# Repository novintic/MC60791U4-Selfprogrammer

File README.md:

This is a take at the MC68701/U4 self- programmer board published in application note AN906A/D by Motorola in 1987.

It allows the 'self-programming' of the MC68701(U4) microcontroller (basically an 6801 with built in Eprom).

Probably the only conceivable use for this thing nowadays is to program a 68701U4 to be used as a replacement for the custom 'PS4' chip on a Bubble Bobble arcade PCB. But if you read this you'll most likely already know that.

MC68701U4s are still more or less readily available on Ebay (either NOS or used).

Some additions and modifications to the original design have been made:
 - redesigned the power supply for the +21V programming voltage using an MC34063 based boost converter circuit
 - uses 27C512 ROMS as these are easily available and dirt cheap
 - Added a Vpp- Voltage LED: will light dim when 5V present and bright wenn 21V Vpp is switched on.

Usage: 
 - Eprom U3 must be programmed with the minprgu4.bin which contains the selfprogramming- code
 - Eprom U4 contains the image to be programmed to the MCU's Eprom (most likely 'a78-01.17' found in the 'bin'- folder).
 - Turn off Power (SW1), put SW2 in 'RESET' position
 - Insert the MC68701U4
 - Switch power on.'PWR' LED should light. 'Vpp' LED will be off (indicating /RST is low)
 - Switch SW2 to 'PRGRM'. 'Vpp' will light dim indicating 5V present at /RST which will take the MCU out of reset and rum minprgu4. At the same time LED 'BLANK' should light indicating blank check. If this check fails, both 'BLANK' and 'FAIL' LEDs will light.
 - If blank- check passes, minprgu4 will switch on Vpp. 'Vpp'- LED will light brightly. Programming of the MCU starts and will take approximately 4 minutes.
 - If programming was successful - which means that the data has been verified correctly - LED 'PASS' will light. If not, LED 'FAIL' will light.

-----------------------------------------------------------------------------------------------
IMPORTANT!

MINPRGU4 must be located from $1850-$1FFF on EPROM U3 (NOT starting from $1800 as the instructions in 'Self-Programming the MC68701/U4 document could be understood).

The Program on U4 must be at $1000-$1FFF on the EPROM U4 for MC68701U4 (for MC68701: $1800-$1FFF)

-----------------------------------------------------------------------------------------------

You can find more info here (also, most of the above changes are based on suggestions from this thread):
https://www.eevblog.com/forum/microcontrollers/self-programming-the-mc68701-and-the-mc68701u4-(motorola)/

This is another quick/messy release. the files have not really been cleaned up. You should be able to upload 'gerber.zip' to your favorite PCB manufacturer.

The board has been tested and works well for us, however, we'll not be able to offer any kind of support.  Please use at your own risk, thank you.

mirko(NOVINTIC) 01/2025

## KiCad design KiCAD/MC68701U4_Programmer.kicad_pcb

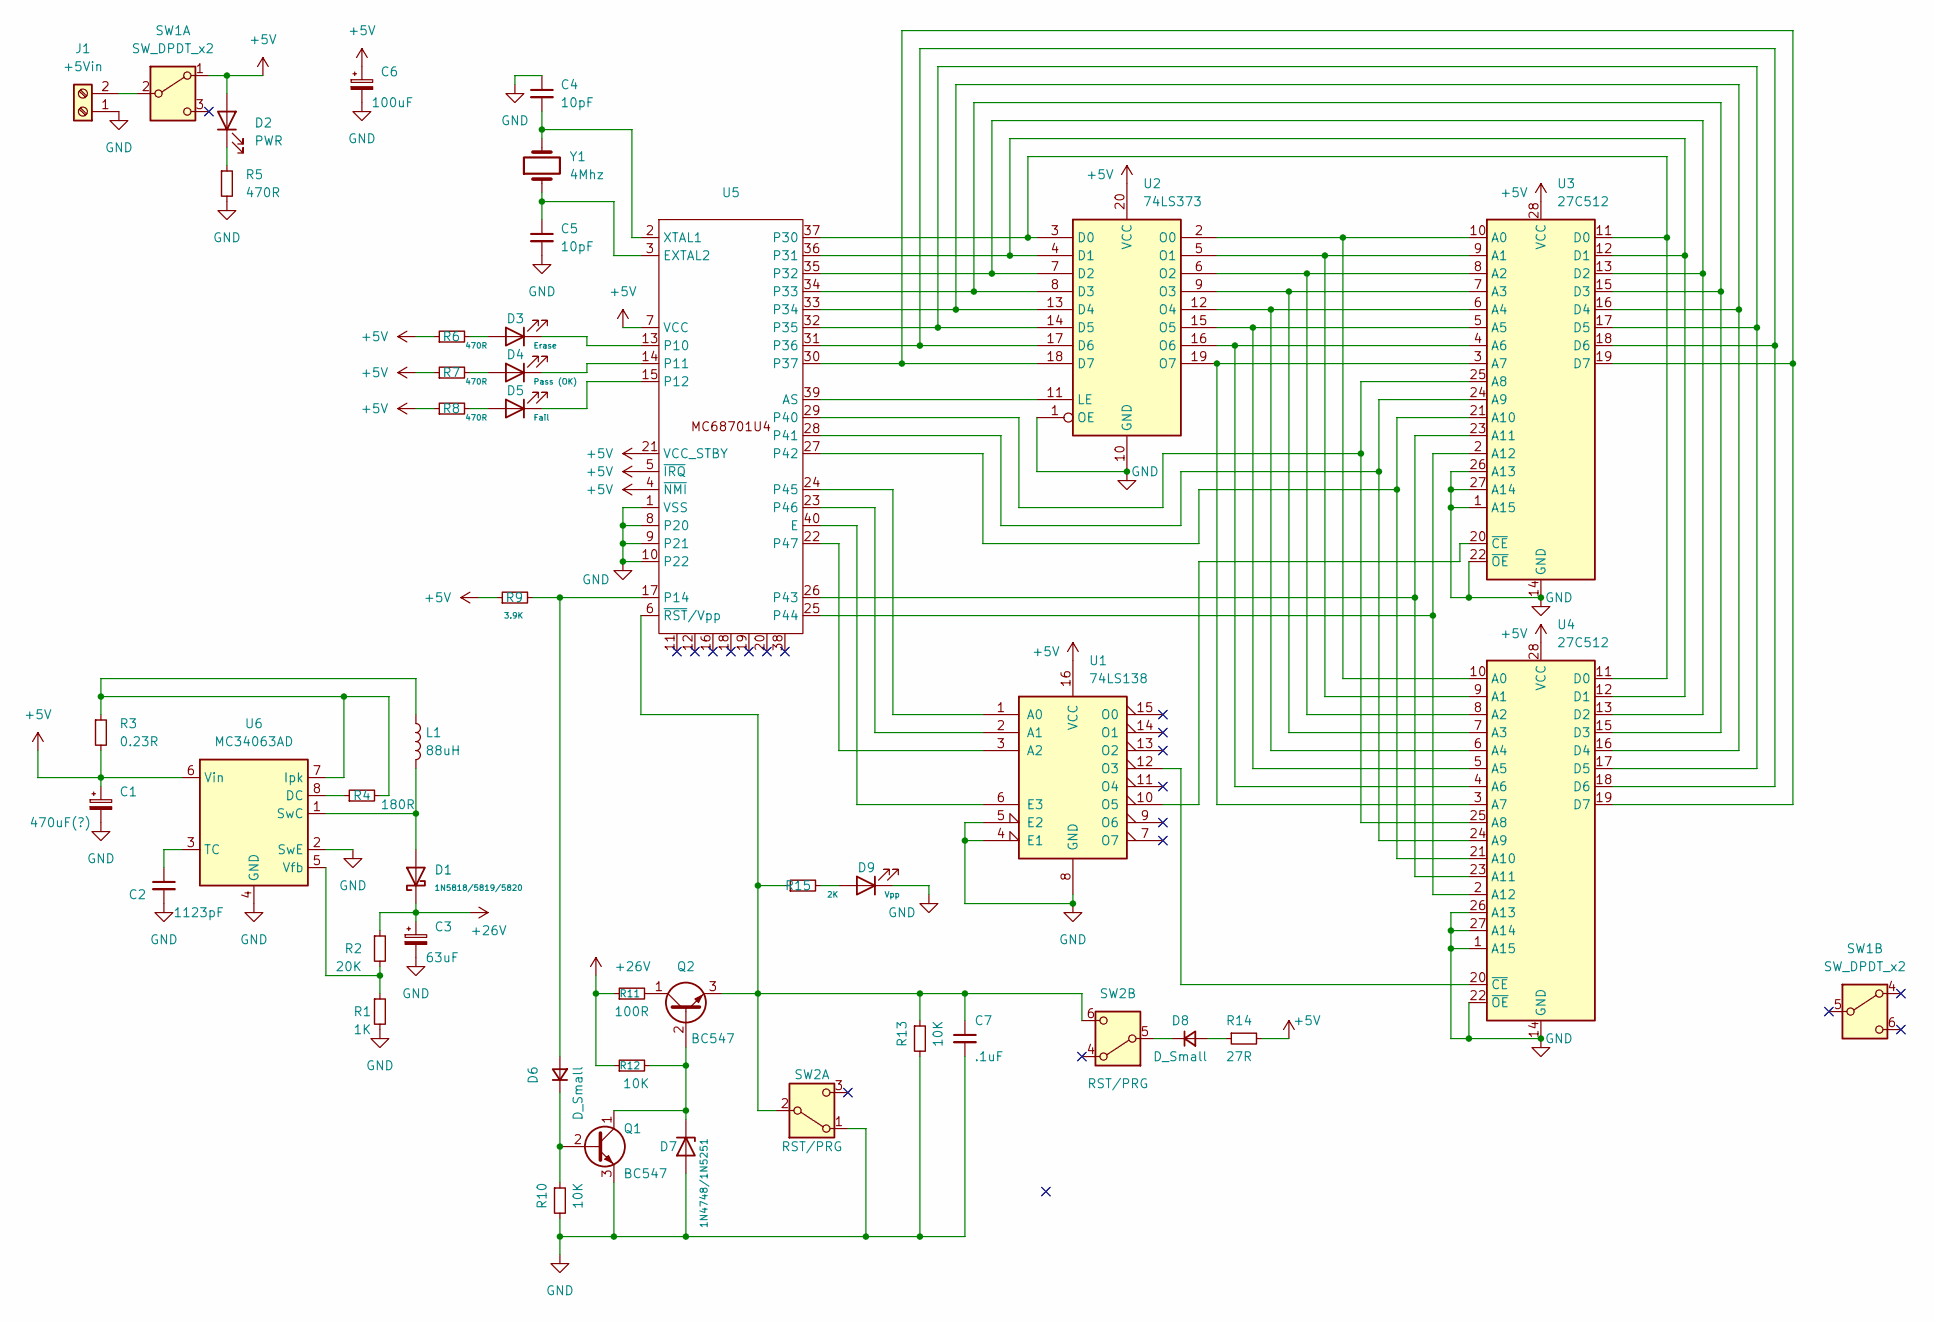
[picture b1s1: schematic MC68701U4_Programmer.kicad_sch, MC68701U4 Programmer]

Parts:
C1: 470uF(?); CP_Radial_D5.0mm_P2.50mm
C2: 1123pF; C_Disc_D3.0mm_W2.0mm_P2.50mm
C3: 63uF; CP_Radial_D5.0mm_P2.50mm
C4, C5: 10pF; C_Disc_D3.0mm_W2.0mm_P2.50mm
C6: 100uF; CP_Radial_D5.0mm_P2.50mm
C7: .1uF; C_Disc_D3.0mm_W2.0mm_P2.50mm
D1: 1N5818/5819/5820; D_DO-34_SOD68_P7.62mm_Horizontal
D2: PWR; LED_D5.0mm_Clear
D3: Erase; LED_D5.0mm
D4: Pass (OK); LED_D5.0mm
D5: Fail; LED_D5.0mm
D6, D8: D_Small; D_DO-34_SOD68_P7.62mm_Horizontal
D7: 1N4748/1N5251; D_DO-34_SOD68_P7.62mm_Horizontal
D9: Vpp; LED_D5.0mm
J1: +5Vin; TerminalBlock_bornier-2_P5.08mm
L1: 88uH; IND_FIT68-1
Q1, Q2: BC547; TO-92_HandSolder
R1: 1K; R_Axial_DIN0207_L6.3mm_D2.5mm_P10.16mm_Horizontal
R2: 20K; R_Axial_DIN0207_L6.3mm_D2.5mm_P10.16mm_Horizontal
R3: 0.23R; R_Axial_DIN0207_L6.3mm_D2.5mm_P10.16mm_Horizontal
R4: 180R; R_Axial_DIN0207_L6.3mm_D2.5mm_P10.16mm_Horizontal
R5, R6, R7, R8: 470R; R_Axial_DIN0207_L6.3mm_D2.5mm_P10.16mm_Horizontal
R9: 3.9K; R_Axial_DIN0207_L6.3mm_D2.5mm_P10.16mm_Horizontal
R10, R12, R13: 10K; R_Axial_DIN0207_L6.3mm_D2.5mm_P10.16mm_Horizontal
R11: 100R; R_Axial_DIN0207_L6.3mm_D2.5mm_P10.16mm_Horizontal
R14: 27R; R_Axial_DIN0207_L6.3mm_D2.5mm_P10.16mm_Horizontal
R15: 2K; R_Axial_DIN0207_L6.3mm_D2.5mm_P10.16mm_Horizontal
SW1: SW_DPDT_x2; SW_GF-126-0159
SW2: RST/PRG; SW_GF-126-0159
U1: 74LS138; DIP-16_W7.62mm_Socket_LongPads
U2: 74LS373; DIP-20_W7.62mm_Socket_LongPads
U3, U4: 27C512; DIP-28_W15.24mm
U5: DIP-40_W15.24mm_Socket_LongPads
U6: MC34063AD; SOIC-8_3.9x4.9mm_P1.27mm
Y1: 4Mhz; Crystal_HC50_Vertical

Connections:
+5V: C1.1, C6.1, D2.2 (A), R3.2, R6.1, R7.1, R8.1, R9.1, R14.2, SW1.1 (A), U1.16 (VCC), U2.20 (VCC), U3.28 (VCC), U4.28 (VCC), U5.4 (~NMI), U5.5 (~IRQ), U5.7 (VCC), U5.21 (VCC_STBY), U6.6 (Vin)
+26V: C3.1, D1.1 (K), R2.1, R11.1, R12.1
GND: C1.2, C2.2, C3.2, C4.1, C5.2, C6.2, C7.2, D7.2 (A), D9.1 (K), J1.1, Q1.3 (E), R1.2, R5.2, R10.2, R13.2, SW2.1 (A), U1.4 (E1), U1.5 (E2), U1.8 (GND), U2.1 (OE), U2.10 (GND), U3.1 (A15), U3.14 (GND), U3.22 (~OE), U3.26 (A13), U3.27 (A14), U4.1 (A15), U4.14 (GND), U4.22 (~OE), U4.26 (A13), U4.27 (A14), U5.1 (VSS), U5.8 (P20), U5.9 (P21), U5.10 (P22), U6.2 (SwE), U6.4 (GND)
unnamed: D1.2 (A), L1.2, U6.1 (SwC)
unnamed: D2.1 (K), R5.1
unnamed: D3.2 (A), R6.2
unnamed: D3.1 (K), U5.13 (P10)
unnamed: D4.2 (A), R7.2
unnamed: D4.1 (K), U5.14 (P11)
unnamed: D5.2 (A), R8.2
unnamed: D5.1 (K), U5.15 (P12)
unnamed: D6.2 (A), R9.2, U5.17 (P14)
unnamed: D6.1 (K), Q1.2 (B), R10.1
unnamed: D7.1 (K), Q1.1 (C), Q2.2 (B), R12.2
unnamed: D8.2 (A), R14.1
unnamed: D8.1 (K), SW2.5 (B)
unnamed: D9.2 (A), R15.2
unnamed: J1.2, SW1.2 (B)
unnamed: Q2.1 (C), R11.2
unnamed: C7.1, Q2.3 (E), R13.1, R15.1, SW2.2 (B), SW2.6 (C), U5.6 (~RST/Vpp)
unnamed: U1.1 (A0), U5.24 (P45)
unnamed: U1.2 (A1), U5.23 (P46)
unnamed: U1.3 (A2), U5.22 (P47)
unnamed: U1.6 (E3), U5.40 (E)
unnamed: U1.12 (O3), U4.20 (~CE)
unnamed: U1.10 (O5), U3.20 (~CE)
unnamed: U2.3 (D0), U3.11 (D0), U4.11 (D0), U5.37 (P30)
unnamed: U2.4 (D1), U3.12 (D1), U4.12 (D1), U5.36 (P31)
unnamed: U2.7 (D2), U3.13 (D2), U4.13 (D2), U5.35 (P32)
unnamed: U2.8 (D3), U3.15 (D3), U4.15 (D3), U5.34 (P33)
unnamed: U2.13 (D4), U3.16 (D4), U4.16 (D4), U5.33 (P34)
unnamed: U2.14 (D5), U3.17 (D5), U4.17 (D5), U5.32 (P35)
unnamed: U2.17 (D6), U3.18 (D6), U4.18 (D6), U5.31 (P36)
unnamed: U2.18 (D7), U3.19 (D7), U4.19 (D7), U5.30 (P37)
unnamed: U2.11 (LE), U5.39 (AS)
unnamed: U2.2 (O0), U3.10 (A0), U4.10 (A0)
unnamed: U2.5 (O1), U3.9 (A1), U4.9 (A1)
unnamed: U2.6 (O2), U3.8 (A2), U4.8 (A2)
unnamed: U2.9 (O3), U3.7 (A3), U4.7 (A3)
unnamed: U2.12 (O4), U3.6 (A4), U4.6 (A4)
unnamed: U2.15 (O5), U3.5 (A5), U4.5 (A5)
unnamed: U2.16 (O6), U3.4 (A6), U4.4 (A6)
unnamed: U2.19 (O7), U3.3 (A7), U4.3 (A7)
unnamed: U3.25 (A8), U4.25 (A8), U5.29 (P40)
unnamed: U3.24 (A9), U4.24 (A9), U5.28 (P41)
unnamed: U3.21 (A10), U4.21 (A10), U5.27 (P42)
unnamed: U3.23 (A11), U4.23 (A11), U5.26 (P43)
unnamed: U3.2 (A12), U4.2 (A12), U5.25 (P44)
unnamed: C5.1, U5.3 (EXTAL2), Y1.1
unnamed: C4.2, U5.2 (XTAL1), Y1.2
unnamed: R4.1, U6.8 (DC)
unnamed: L1.1, R3.1, R4.2, U6.7 (Ipk)
unnamed: C2.1, U6.3 (TC)
unnamed: R1.1, R2.2, U6.5 (Vfb)

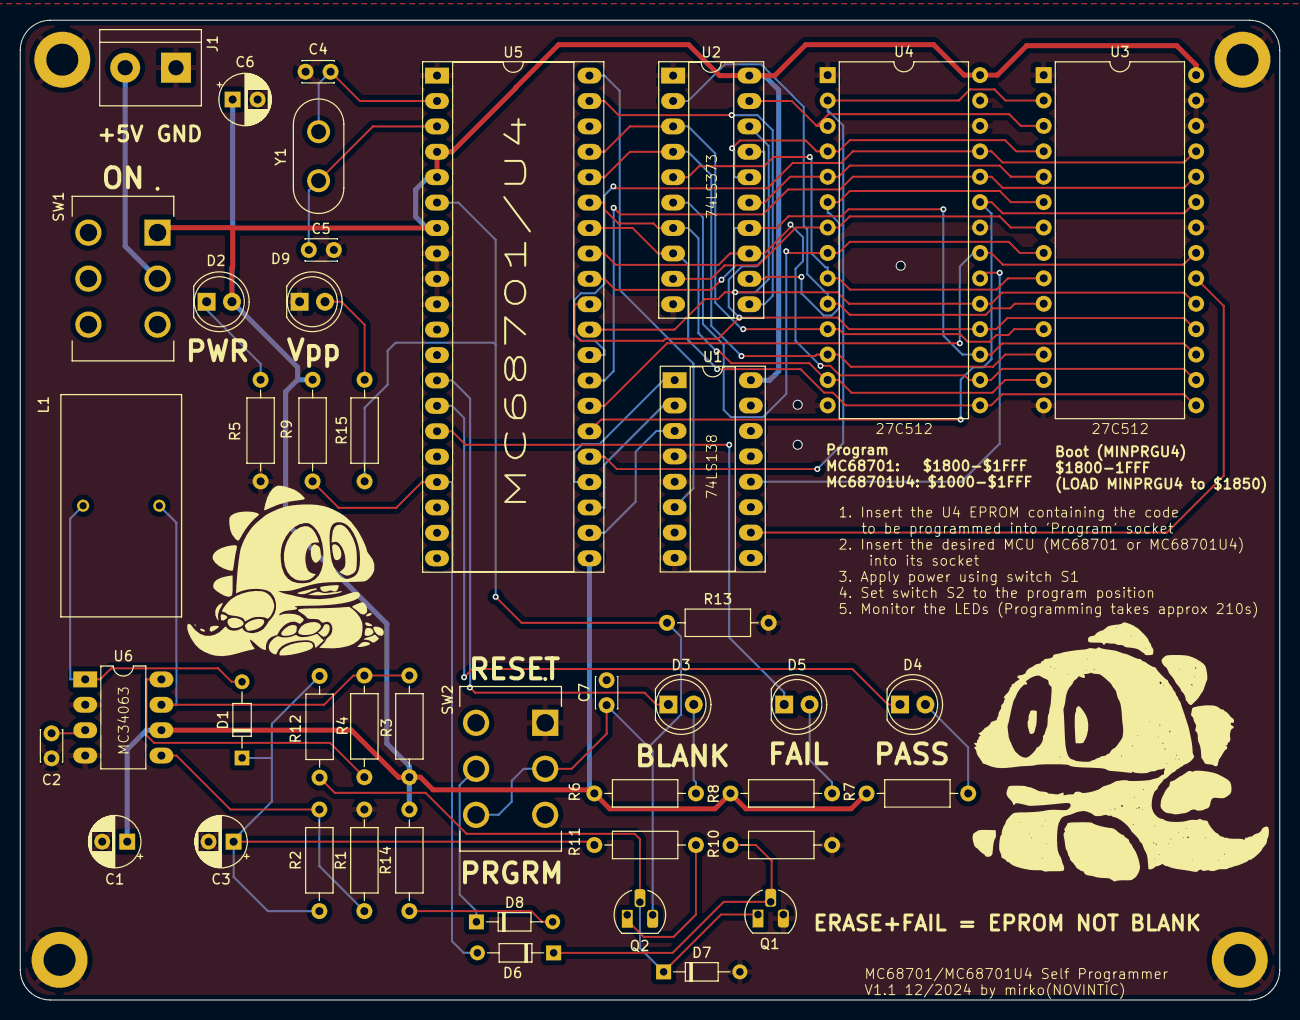
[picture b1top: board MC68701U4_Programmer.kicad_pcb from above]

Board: 2 copper layers, 125.9 x 98.0 mm, 44 parts (0 on the bottom side), 54 nets.
